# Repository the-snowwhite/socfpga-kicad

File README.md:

# socfpga-kicad
Hardware addons for mksocfpga

Schematic for GPIO -> Cramps Interface

[Cramps2_nano-soc2_pcb 3D view](Cramps2nano-soc/Cramps2_nano-soc2_pcb.stl)

---

Schematic and pcb designs for Capasitive touch sensor (for depth probing)

PCB's can be ordered from SeeedStudio:
https://www.seeedstudio.com/Capsense-Touchsense-g-1222872

---
Trinamic BOB mounting pcb's

---

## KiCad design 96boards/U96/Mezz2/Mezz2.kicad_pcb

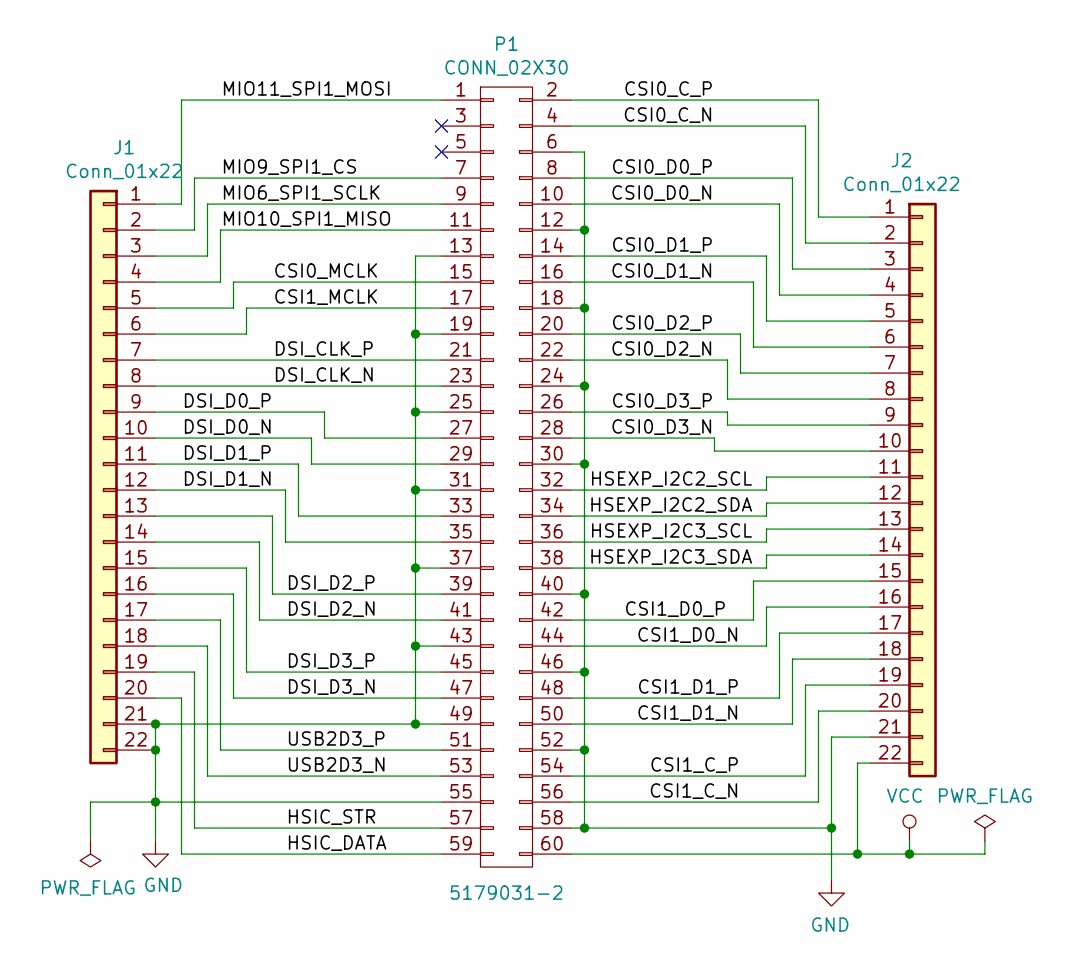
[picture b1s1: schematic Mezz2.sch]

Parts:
J1, J2: Conn_01x22; PinHeader_1x22_P2.54mm_Vertical; MPN PBC22SABN
P1: CONN_02X30; 61083-063400LF; MPN 5179031-2

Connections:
/ CSI1_D0_N: J2.16, P1.44
/ CSI1_D0_P: J2.15, P1.42
/CSI0_C_N: J2.2, P1.4
/CSI0_C_P: J2.1, P1.2
/CSI0_D0_N: J2.4, P1.10
/CSI0_D0_P: J2.3, P1.8
/CSI0_D1_N: J2.6, P1.16
/CSI0_D1_P: J2.5, P1.14
/CSI0_D2_N: J2.8, P1.22
/CSI0_D2_P: J2.7, P1.20
/CSI0_D3_N: J2.10, P1.28
/CSI0_D3_P: J2.9, P1.26
/CSI0_MCLK: J1.5, P1.15
/CSI1_C_N: J2.20, P1.56
/CSI1_C_P: J2.19, P1.54
/CSI1_D1_N: J2.18, P1.50
/CSI1_D1_P: J2.17, P1.48
/CSI1_MCLK: J1.6, P1.17
/DSI_CLK_N: J1.8, P1.23
/DSI_CLK_P: J1.7, P1.21
/DSI_D0_N: J1.10, P1.29
/DSI_D0_P: J1.9, P1.27
/DSI_D1_N: J1.12, P1.35
/DSI_D1_P: J1.11, P1.33
/DSI_D2_N: J1.14, P1.41
/DSI_D2_P: J1.13, P1.39
/DSI_D3_N: J1.16, P1.47
/DSI_D3_P: J1.15, P1.45
/HSEXP_I2C2_SCL: J2.11, P1.32
/HSEXP_I2C2_SDA: J2.12, P1.34
/HSEXP_I2C3_SCL: J2.13, P1.36
/HSEXP_I2C3_SDA: J2.14, P1.38
/HSIC_DATA: J1.20, P1.59
/HSIC_STR: J1.19, P1.57
/MIO6_SPI1_SCLK: J1.3, P1.9
/MIO9_SPI1_CS: J1.2, P1.7
/MIO10_SPI1_MISO: J1.4, P1.11
/MIO11_SPI1_MOSI: J1.1, P1.1
/USB2D3_N: J1.18, P1.53
/USB2D3_P: J1.17, P1.51
GND: J1.21, J1.22, J2.21, P1.6, P1.12, P1.13, P1.18, P1.19, P1.24, P1.25, P1.30, P1.31, P1.37, P1.40, P1.43, P1.46, P1.49, P1.52, P1.55, P1.58
VCC: J2.22, P1.60

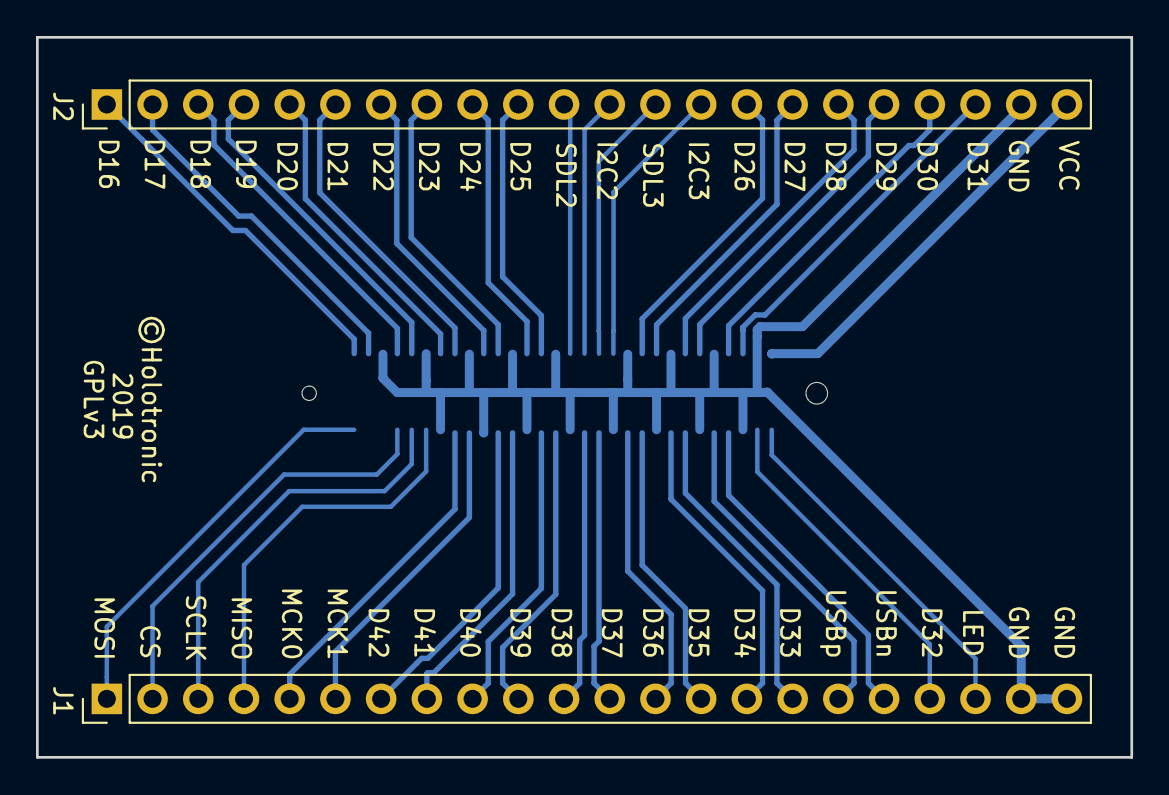
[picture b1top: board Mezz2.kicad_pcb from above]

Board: 2 copper layers, 60.8 x 40.0 mm, 3 parts (1 on the bottom side), 42 nets.

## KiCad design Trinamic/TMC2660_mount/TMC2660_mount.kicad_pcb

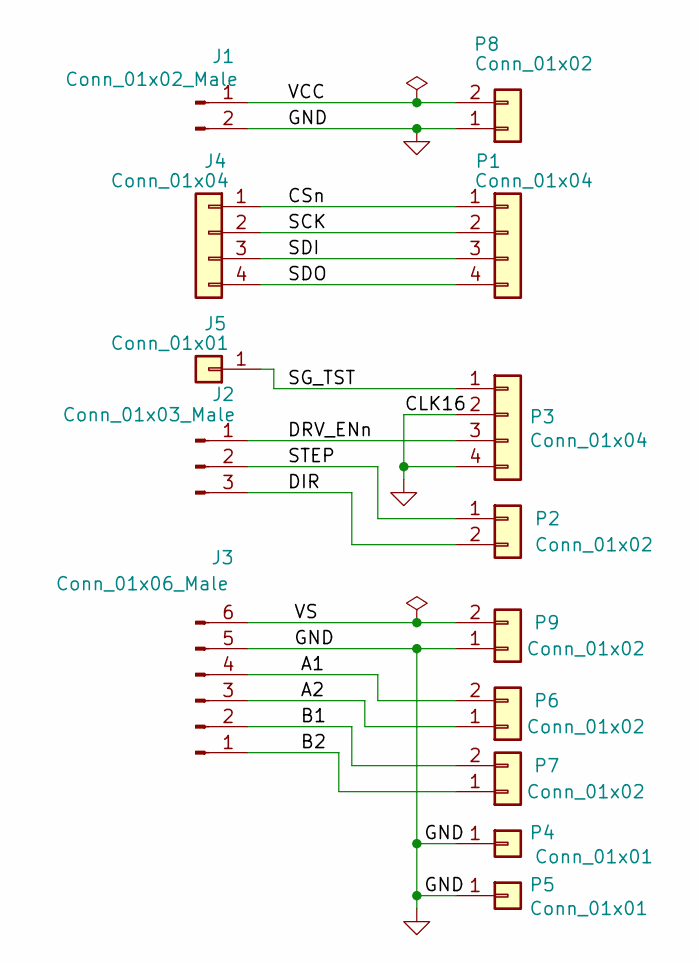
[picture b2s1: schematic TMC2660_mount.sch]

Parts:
J1: Conn_01x02_Male; TerminalBlock_bornier-2_P5.08mm
J2: Conn_01x03_Male; TerminalBlock_bornier-3_P5.08mm
J3: Conn_01x06_Male; TerminalBlock_bornier-6_P5.08mm
J4: Conn_01x04; PinSocket_1x04_P2.54mm_Vertical_Shrouded-4_Wall_Latch_Holder
J5: Conn_01x01; PinHeader_1x01_P2.54mm_Horizontal
P1, P3: Conn_01x04; PinSocket_1x04_P2.54mm_Vertical
P2, P6, P7, P8, P9: Conn_01x02; PinSocket_1x02_P2.54mm_Vertical
P4, P5: Conn_01x01; PinSocket_1x01_P2.54mm_Vertical

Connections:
/A1: J3.4, P6.2
/A2: J3.3, P6.1
/B1: J3.2, P7.2
/B2: J3.1, P7.1
/CSn: J4.1, P1.1
/DIR: J2.3, P2.2
/DRV_ENn: J2.1, P3.3
/SCK: J4.2, P1.2
/SDI: J4.3, P1.3
/SDO: J4.4, P1.4
/SG_TST: J5.1, P3.1
/STEP: J2.2, P2.1
/VCC: J1.1, P8.2
/VS: J3.6, P9.2
GND: J1.2, J3.5, P3.2, P3.4, P4.1, P5.1, P8.1, P9.1

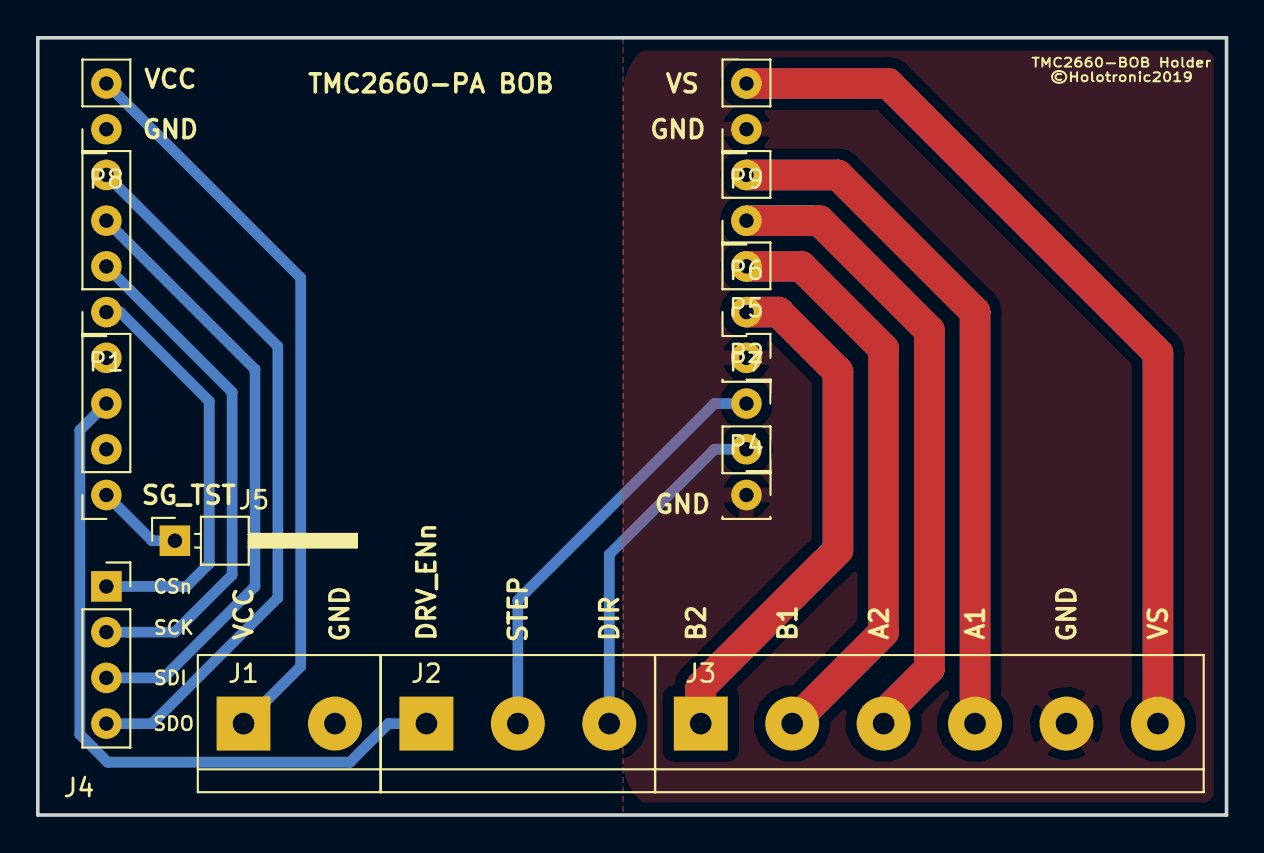
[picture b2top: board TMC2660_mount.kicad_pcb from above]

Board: 2 copper layers, 66.0 x 43.2 mm, 14 parts (0 on the bottom side), 15 nets.

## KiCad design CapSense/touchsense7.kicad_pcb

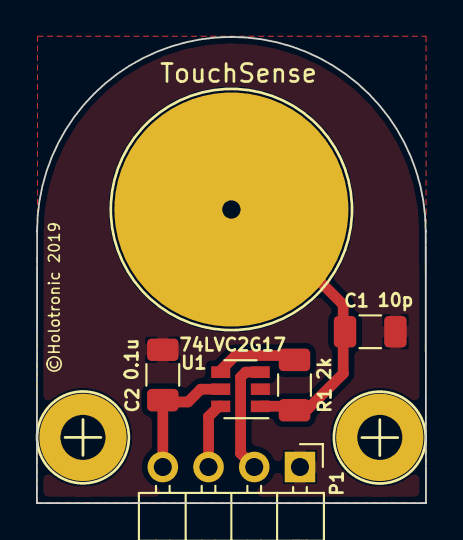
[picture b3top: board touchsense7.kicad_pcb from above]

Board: 2 copper layers, 21.6 x 25.9 mm, 8 parts (0 on the bottom side), 6 nets.

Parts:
C1: 10p; C_1206_3216Metric
C2: 0.1u; C_1206_3216Metric
P1: CONN_01X04; PinHeader_1x04_P2.54mm_Horizontal
P2: TouchSense; 1pin_pad-round_s
R1: 2k; R_1206_3216Metric
S1, S1#2: Screw; Screw_2.5mm
U1: 74LVC2G17; SOT-23-6

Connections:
GND: C1.2, C2.2, P1.1, U1.2
unnamed: C1.1, P2.1, R1.1, U1.1
unnamed: P1.2, U1.3
unnamed: P1.3, U1.6
unnamed: R1.2, U1.4
VCC: C2.1, P1.4, U1.5

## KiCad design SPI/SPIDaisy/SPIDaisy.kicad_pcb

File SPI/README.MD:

LTC-SPI Interface boards to use Machinekit Mksocfpga DExx_Nano boards
with trinamic spi configurable step drivers

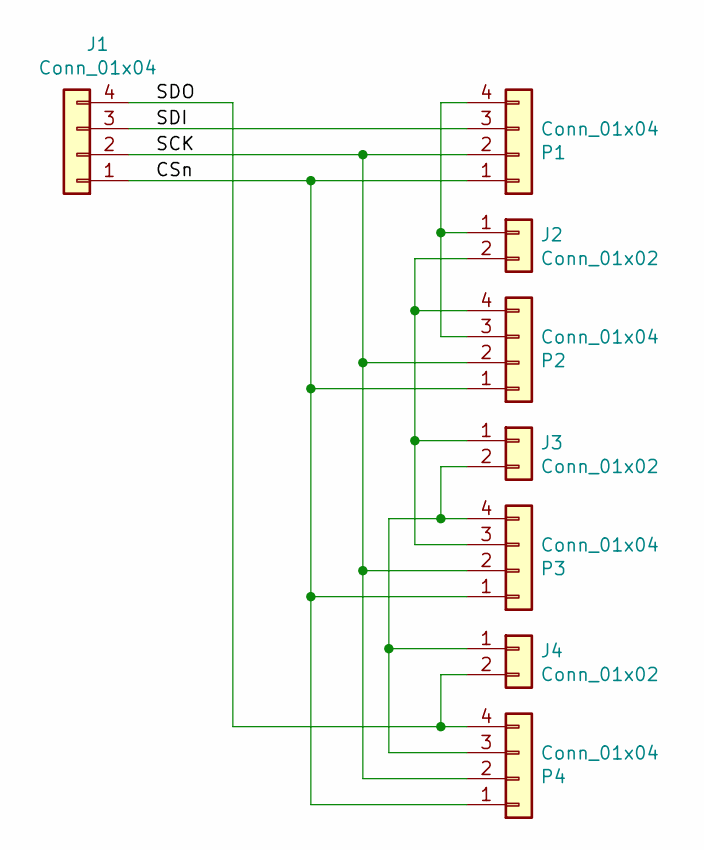
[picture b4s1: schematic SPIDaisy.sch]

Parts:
J1: Conn_01x04; PinSocket_1x04_P2.54mm_Vertical_Shrouded-4_Wall_Latch_Holder
J2, J3, J4: Conn_01x02; PinHeader_1x02_P2.54mm_Vertical
P1, P2, P3, P4: Conn_01x04; PinSocket_1x04_P2.54mm_Vertical_Shrouded-4_Wall_Latch_Holder

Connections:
/CSn: J1.1, P1.1, P2.1, P3.1, P4.1
/SCK: J1.2, P1.2, P2.2, P3.2, P4.2
/SDI: J1.3, P1.3
/SDO: J1.4, J4.2, P4.4
unnamed: J2.1, P1.4, P2.3
unnamed: J2.2, J3.1, P2.4, P3.3
unnamed: J3.2, J4.1, P3.4, P4.3

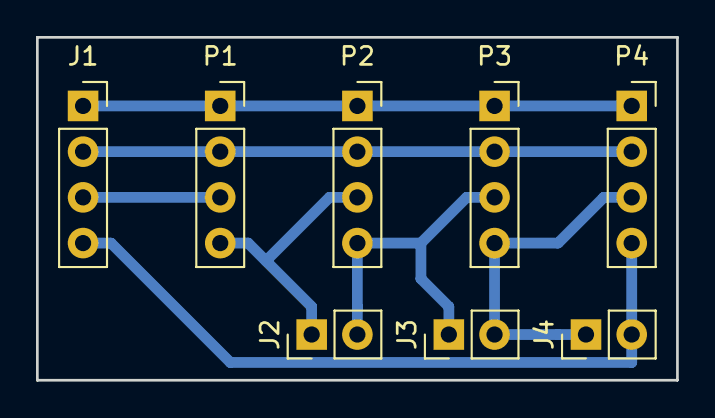
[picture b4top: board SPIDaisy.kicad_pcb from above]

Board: 2 copper layers, 35.6 x 19.1 mm, 8 parts (0 on the bottom side), 7 nets.

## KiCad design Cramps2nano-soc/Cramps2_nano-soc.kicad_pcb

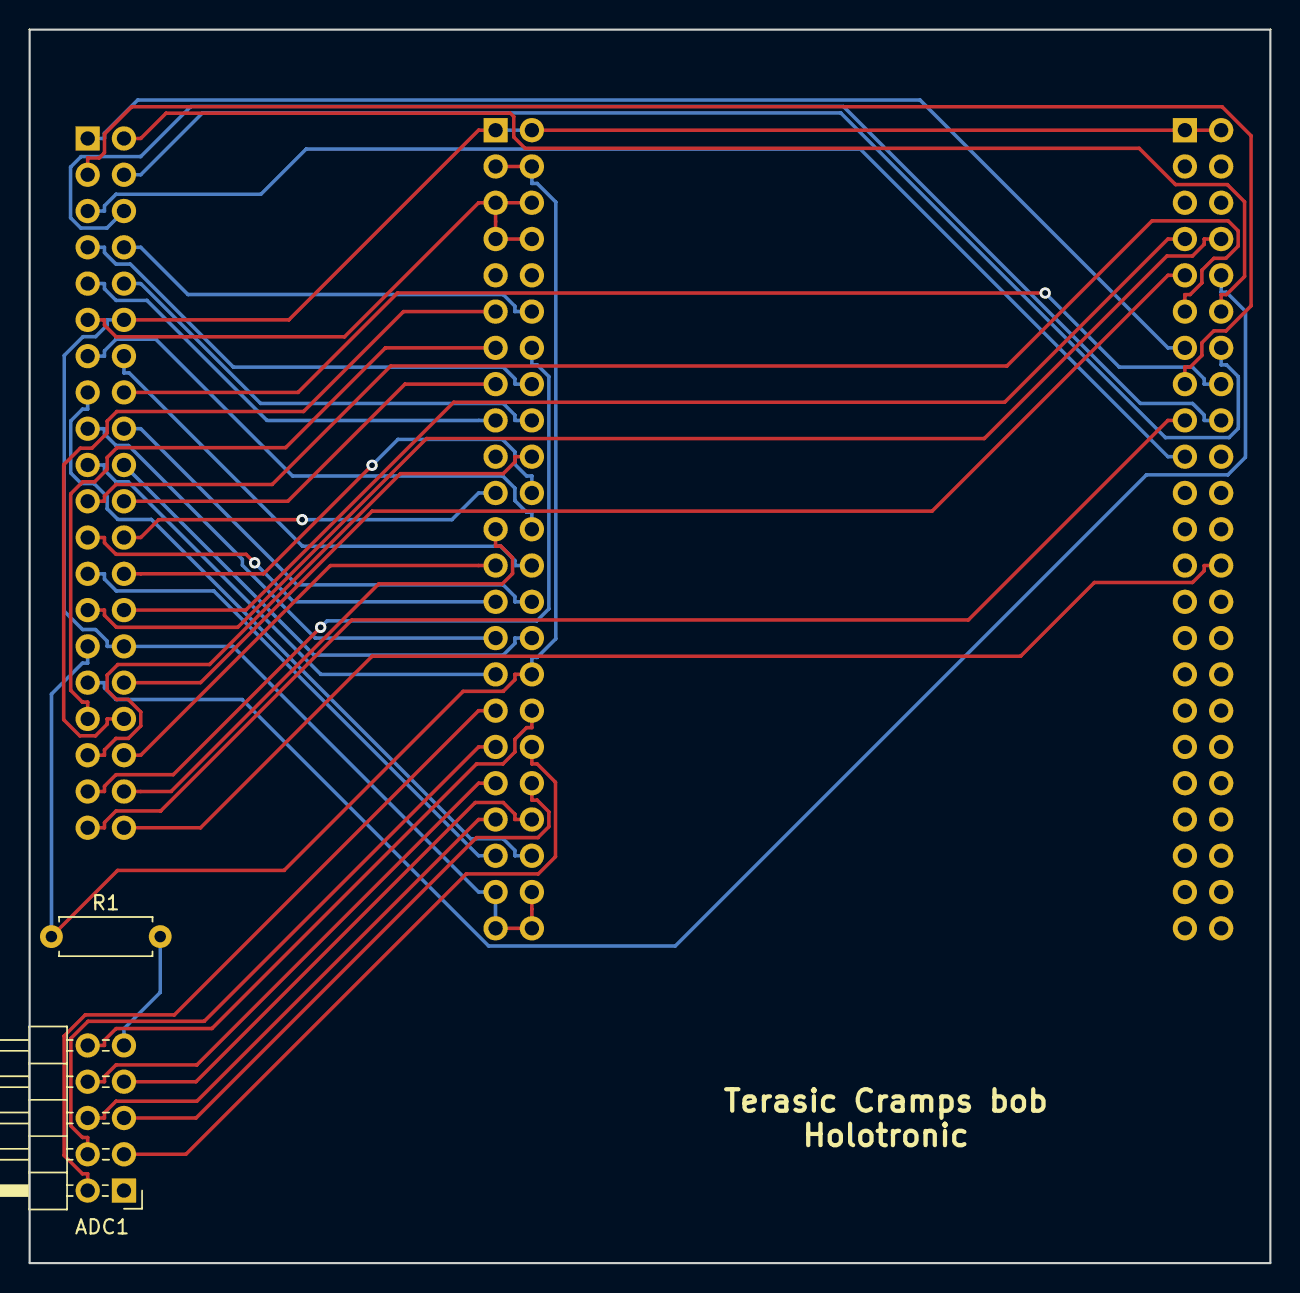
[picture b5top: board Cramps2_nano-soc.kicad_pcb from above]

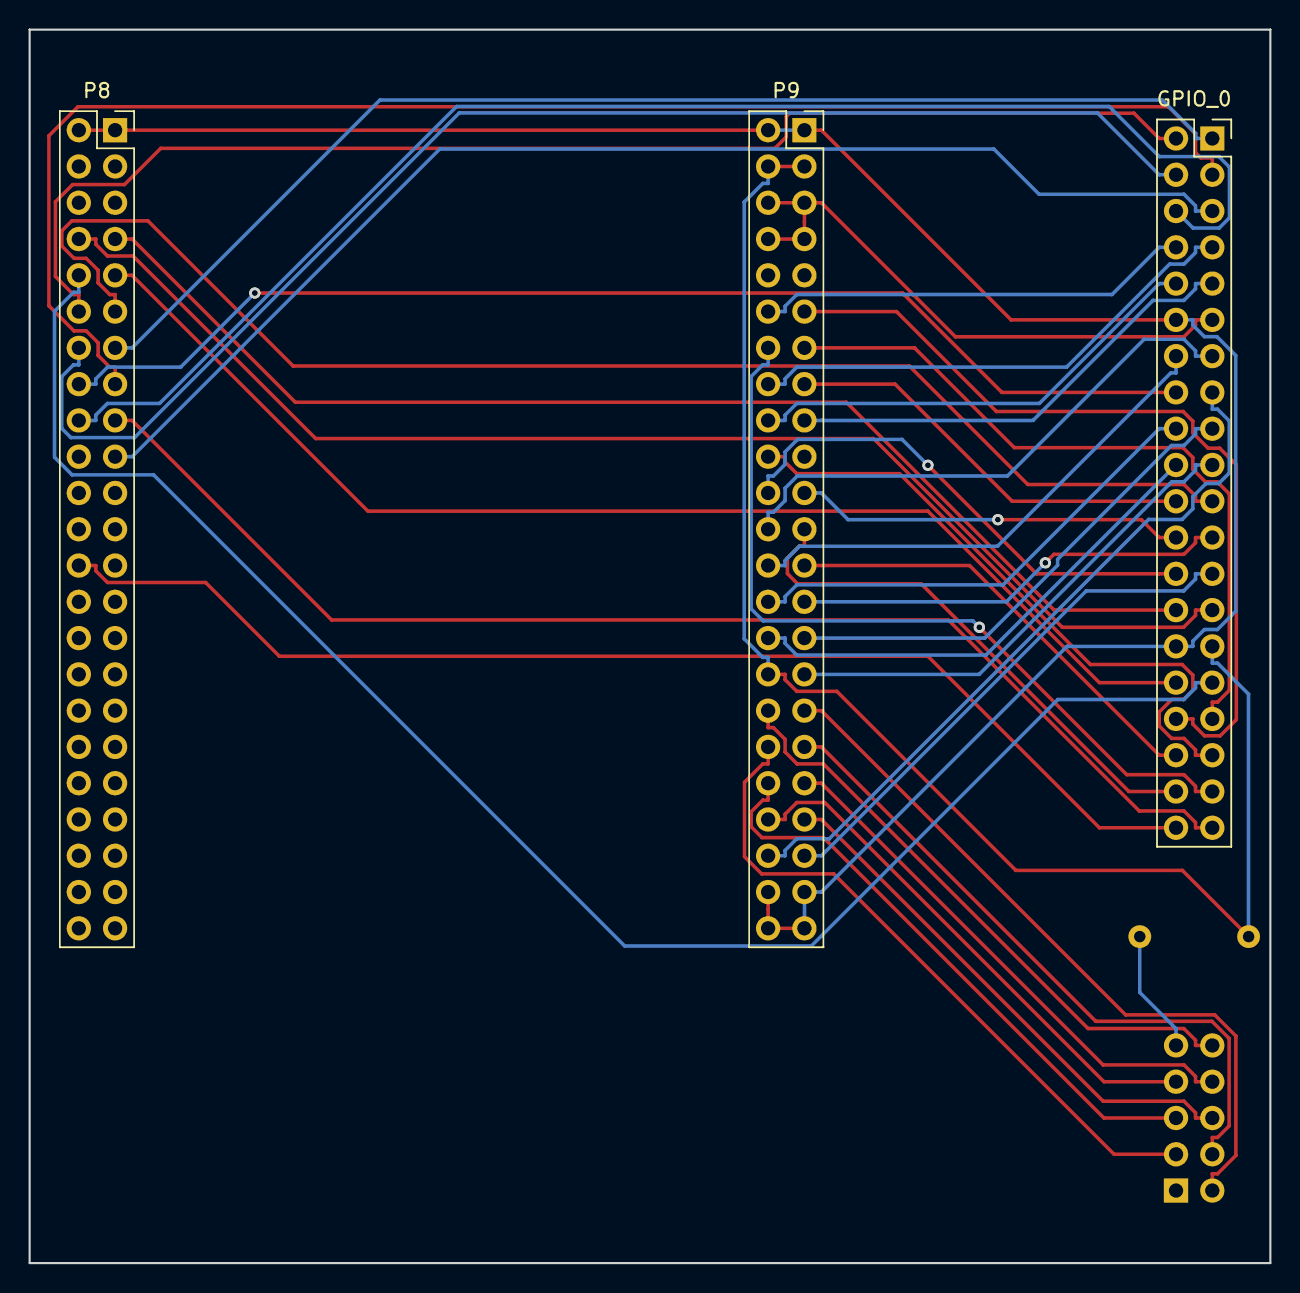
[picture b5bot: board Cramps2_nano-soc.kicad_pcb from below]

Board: 2 copper layers, 86.9 x 86.4 mm, 5 parts (3 on the bottom side), 48 nets.

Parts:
ADC1: CONN_02X05; PinHeader_2x05_P2.54mm_Horizontal
GPIO_0: CONN_02X20; PinSocket_2x20_P2.54mm_Vertical
P8, P9: BB_EXP_CONN; PinSocket_2x23_P2.54mm_Vertical
R1: 120R; R_Axial_DIN0207_L6.3mm_D2.5mm_P7.62mm_Horizontal

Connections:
ADC_GND: ADC1.10, P9.34
ADC_VDD: GPIO_0.29, P9.3, P9.4, P9.32, R1.1
AIN0: ADC1.6, P9.39
AIN1: ADC1.7, P9.40
AIN2: ADC1.8, P9.37
AIN3: ADC1.5, P9.38
AXIS_ENAn: GPIO_0.37, P9.14
DGND: GPIO_0.12, GPIO_0.30, P8.1, P8.2, P9.1, P9.2, P9.43, P9.44, P9.45, P9.46
DIR_U: GPIO_0.16, P8.16
DIR_V: GPIO_0.18, P9.28
DIR_W: GPIO_0.20, P9.30
E0_DIR: GPIO_0.8, P9.12
E0_STEP: GPIO_0.7, P9.16
E1_DIR: GPIO_0.10, P9.18
E1_STEP: GPIO_0.9, P9.17
E2_DIR: GPIO_0.14, P9.26
E2_STEP: GPIO_0.13, P9.24
ESTOP: GPIO_0.39, P8.17
ESTOP_SW: GPIO_0.40, P8.26
FET1: GPIO_0.21, P8.11
FET2: GPIO_0.22, P9.15
FET3: GPIO_0.23, P9.27
FET4: GPIO_0.24, P9.21
FET5: GPIO_0.25, P9.41
FET6: GPIO_0.26, P9.22
LED: GPIO_0.36, P9.25
MACHINE_PWR: GPIO_0.38, P9.23
unnamed: ADC1.9, R1.2
SDA: GPIO_0.35, P9.20
STEP_U: GPIO_0.15, P9.42
STEP_V: GPIO_0.17, P9.29
STEP_W: GPIO_0.19, P9.31
SYS_5V: GPIO_0.11, P9.5, P9.6, P9.7, P9.8
THERM0: ADC1.2, P9.33
THERM1: ADC1.3, P9.36
THERM2: ADC1.4, P9.35
X-MAX: GPIO_0.28, P8.7
X-MIN: GPIO_0.27, P8.8
X_DIR: GPIO_0.2, P8.12
X_STEP: GPIO_0.1, P8.13
Y-MAX: GPIO_0.32, P8.9
Y-MIN: GPIO_0.31, P8.10
Y_DIR: GPIO_0.4, P8.14
Y_STEP: GPIO_0.3, P8.15
Z-MAX: GPIO_0.34, P9.11
Z-MIN: GPIO_0.33, P9.13
Z_DIR: GPIO_0.6, P8.18
Z_STEP: GPIO_0.5, P8.19

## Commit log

2017-08-15 add 3.3 voltage ref resistor on adc ch 8
2017-08-23 Add Cramps2Nano schematic pdf print out
2019-04-21 Add version 2
2019-04-21 add symbol tables
2019-04-22 Add rescue-backup folder
2019-04-22 Add 3d presentation file (stl)
2019-04-22 Update stl file and add .step files made by kicad and freecad
2019-04-23 Added DExx_Nano LTC interface and spi daisy chain interfaces (for trinamic spi step drivers)
2019-04-23 Added readme for SPI boards
2019-05-13 Rename: Touch-sense2 folder to CapSense and add newest work
2019-05-13 Add pdf of schematic
2019-05-13 Update LICENSE
2019-08-19 Add DExx_Nano board templates
2019-08-19 Add TMC 26xx mounting pcb's
2019-08-19 Update cache file
2019-08-19 Update cache file's
2019-08-19 Add images
2019-08-19 Add image
2019-09-22 Add 96boards Mezzanine bob

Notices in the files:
96boards/U96/Mezz2/Mezz2.kicad_pcb:
©Holotronic
GPLv3
CapSense/touchsense7.kicad_pcb:
©Holotronic 2019
